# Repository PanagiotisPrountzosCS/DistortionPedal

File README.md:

# Custom distortion pedal implemented in kicad and ltspice

## This pedal is comprised of 3 stages:
  - Amplification
  - Clipping
  - Output Filtering

## The main branch contains a 100mm X 100mm PCB, while the 1590b-pcb branch contains a 35mm X 88mm PCB, which fits inside a 1590b box

## 1590b pcb

## 100mmx100mm pcb

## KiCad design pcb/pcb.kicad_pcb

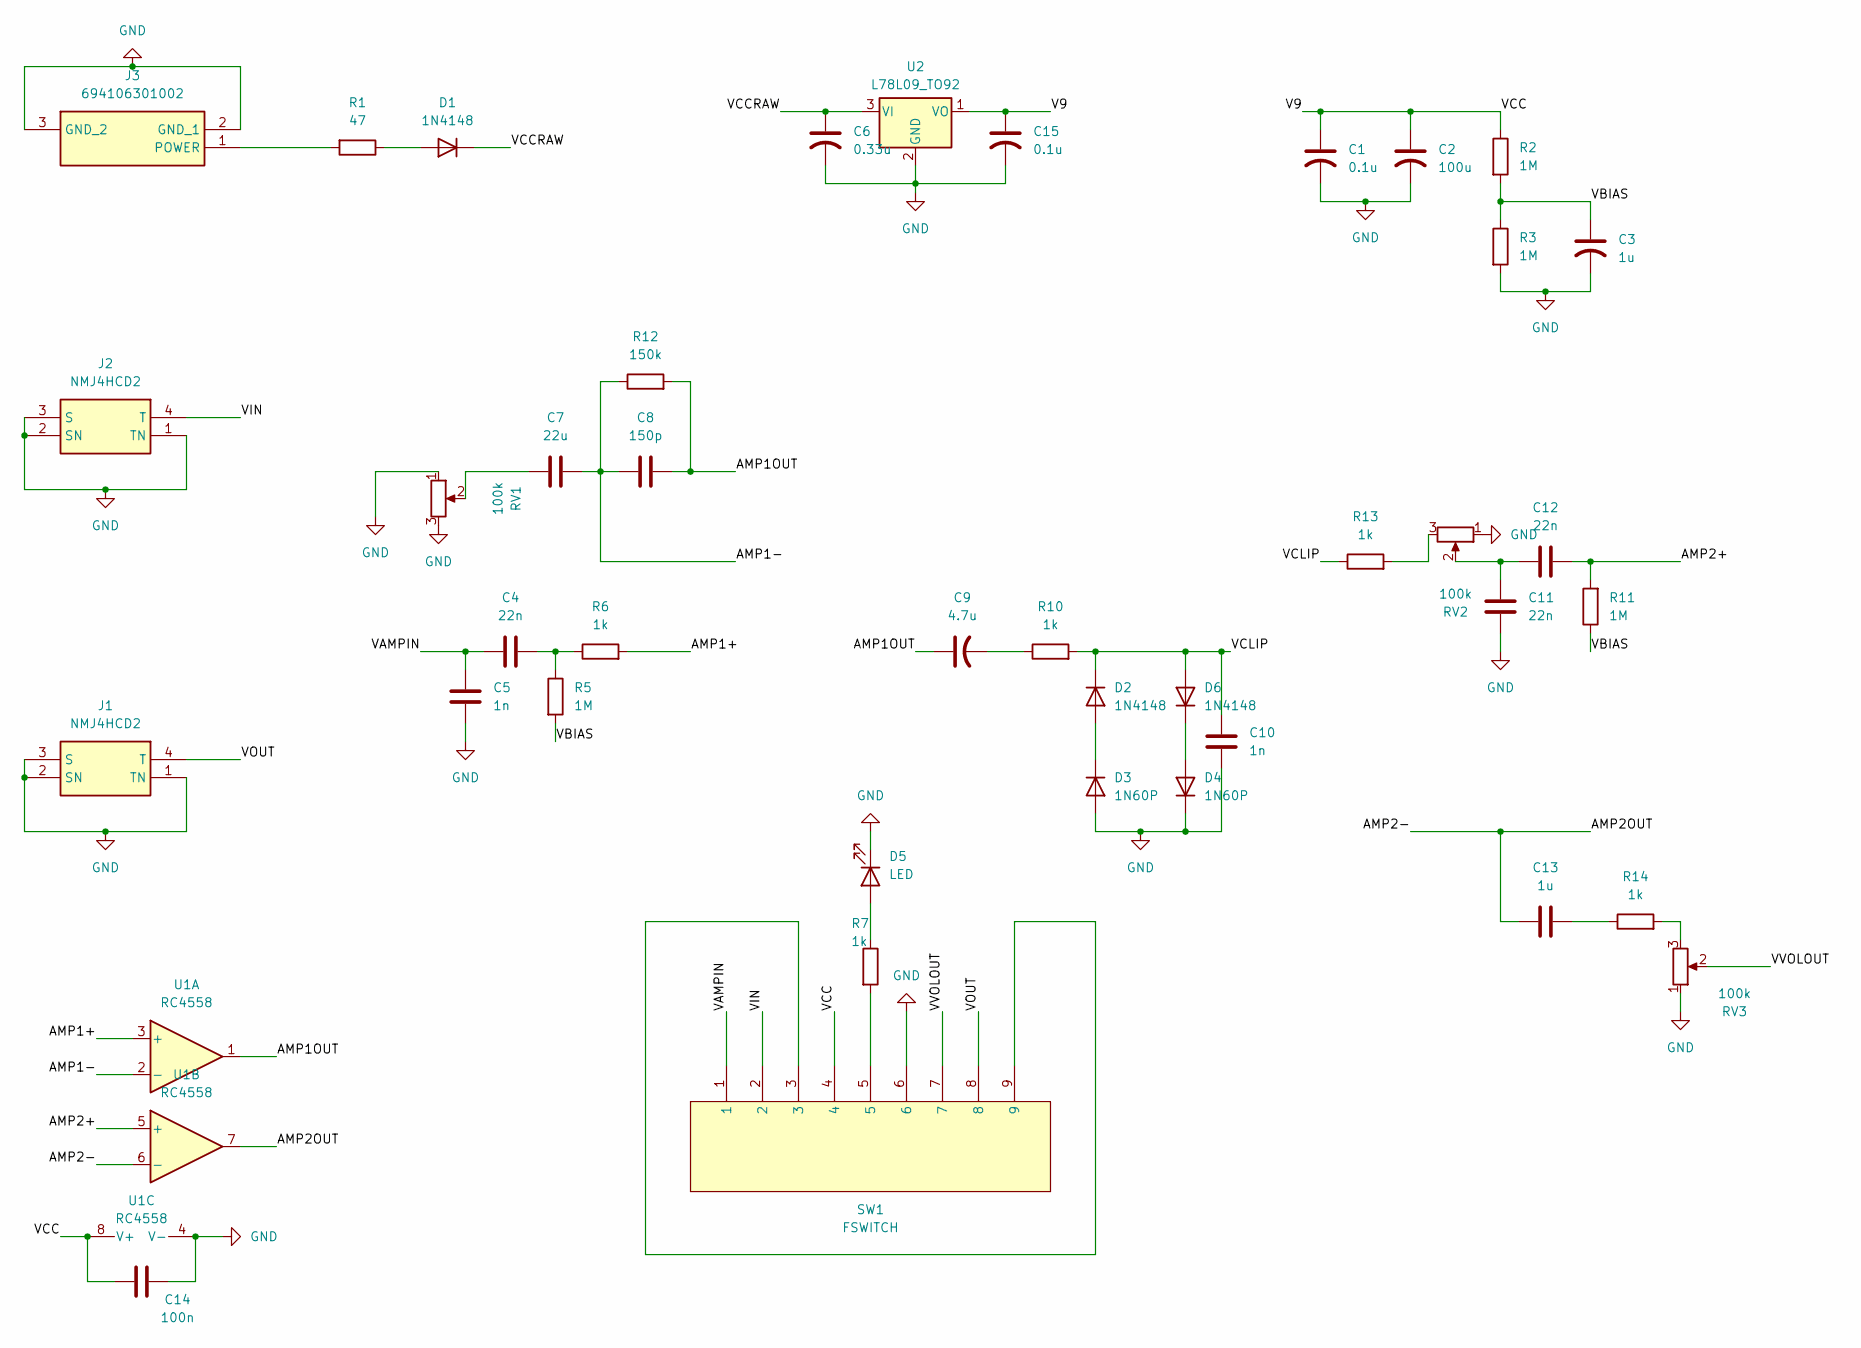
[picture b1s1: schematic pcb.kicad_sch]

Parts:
C1, C15: 0.1u; C_Radial_D5.0mm_H11.0mm_P2.00mm
C2: 100u; C_Radial_D6.3mm_H11.0mm_P2.50mm
C3: 1u; C_Radial_D6.3mm_H11.0mm_P2.50mm
C4, C12: 22n; C_Rect_L7.2mm_W2.5mm_P5.00mm
C5, C10: 1n; C_Disc_D3.0mm_W1.6mm_P2.50mm
C6: 0.33u; C_Radial_D5.0mm_H11.0mm_P2.00mm
C7: 22u; C_Radial_D5.0mm_H11.0mm_P2.00mm
C8: 150p; C_Disc_D3.0mm_W1.6mm_P2.50mm
C9: 4.7u; C_Radial_D5.0mm_H11.0mm_P2.00mm
C11: 22n; C_Disc_D3.0mm_W1.6mm_P2.50mm
C13: 1u; C_Rect_L7.2mm_W2.5mm_P5.00mm
C14: 100n; C_Disc_D3.0mm_W1.6mm_P2.50mm
D1, D2, D6: 1N4148; D_DO-35_SOD27_P7.62mm_Horizontal
D3, D4: 1N60P; D_DO-41_SOD81_P10.16mm_Horizontal
D5: LED; LED_D3.0mm
J1, J2: NMJ4HCD2; Mouser Part Number 550-12202
J3: 694106301002; Mouser Part Number 710-694106301002
R1: 47; R_Axial_DIN0207_L6.3mm_D2.5mm_P10.16mm_Horizontal
R2, R3, R5, R11: 1M; R_Axial_DIN0207_L6.3mm_D2.5mm_P10.16mm_Horizontal
R6, R7, R10, R13, R14: 1k; R_Axial_DIN0207_L6.3mm_D2.5mm_P10.16mm_Horizontal
R12: 150k; R_Axial_DIN0207_L6.3mm_D2.5mm_P10.16mm_Horizontal
RV1, RV2, RV3: 100k; Potentiometer_Omeg_PC16BU_Vertical
SW1: FSWITCH; 3PDT
U1: RC4558; CERDIP-8_W7.62mm_SideBrazed_LongPads_Socket
U2: L78L09_TO92; TO-92_Inline

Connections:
/AMP1+: R6.2, U1.3 (+)
/AMP1-: C7.2, C8.1, R12.1, U1.2 (-)
/AMP1OUT: C8.2, C9.1, R12.2, U1.1
/AMP2+: C12.2, R11.2, U1.5 (+)
/AMP2-: C13.1, U1.6 (-), U1.7
/V9: C1.1, C2.1, C14.2, C15.1, R2.1, SW1.4, U1.8 (V+), U2.1 (VO)
/VAMPIN: C4.1, C5.2, SW1.1
/VBIAS: C3.1, R2.2, R3.1, R5.2, R11.1
/VCCRAW: C6.1, D1.1 (K), U2.3 (VI)
/VCLIP: C10.2, D2.1 (K), D6.2 (A), R10.2, R13.1
/VIN: J2.4 (T), SW1.2
/VOUT: J1.4 (T), SW1.8
/VVOLOUT: RV3.2, SW1.7
GND: C1.2, C2.2, C3.2, C5.1, C6.2, C10.1, C11.2, C14.1, C15.2, D3.2 (A), D4.1 (K), D5.1 (K), J1.1 (TN), J1.2 (SN), J1.3 (S), J2.1 (TN), J2.2 (SN), J2.3 (S), J3.2 (GND_1), J3.3 (GND_2), R3.2, RV1.1, RV1.3, RV2.1, RV3.1, SW1.6, U1.4 (V-), U2.2 (GND)
unnamed: C4.2, R5.1, R6.1
unnamed: C7.1, RV1.2
unnamed: C9.2, R10.1
unnamed: C11.1, C12.1, RV2.2
unnamed: C13.2, R14.1
unnamed: D1.2 (A), R1.1
unnamed: D2.2 (A), D3.1 (K)
unnamed: D4.2 (A), D6.1 (K)
unnamed: D5.2 (A), R7.1
unnamed: J3.1 (POWER), R1.2
unnamed: R7.2, SW1.5
unnamed: R13.2, RV2.3
unnamed: R14.2, RV3.3
unnamed: SW1.3, SW1.9

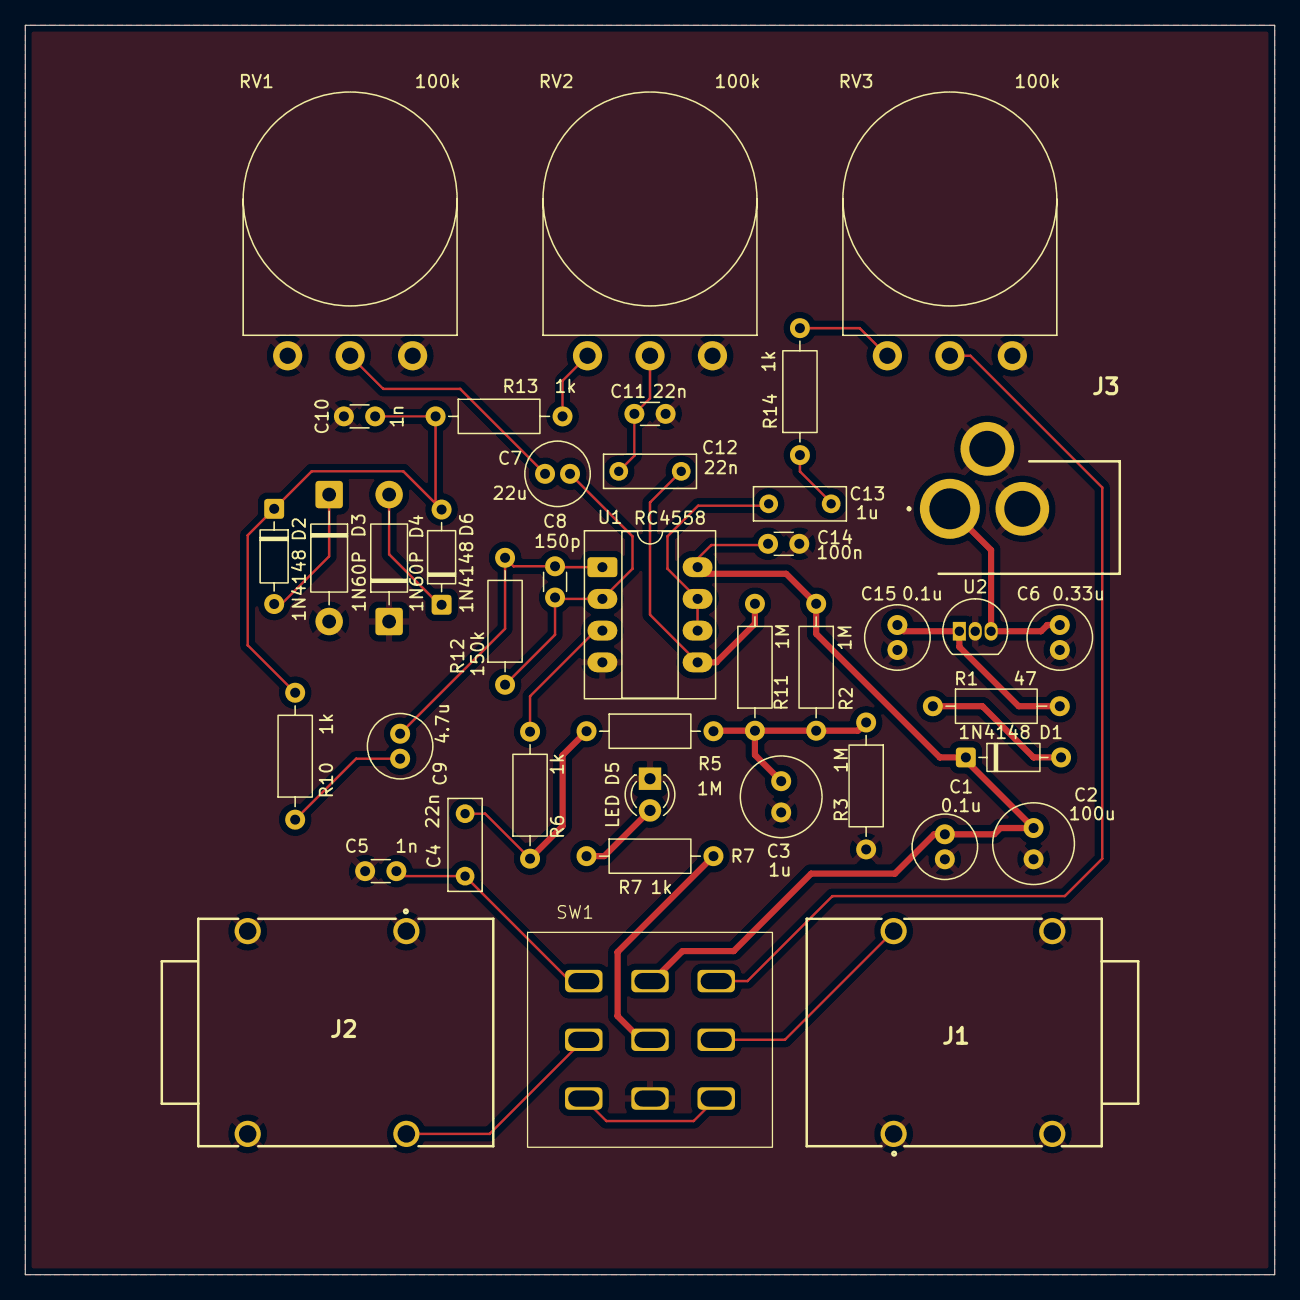
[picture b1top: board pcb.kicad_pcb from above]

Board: 2 copper layers, 100.0 x 100.0 mm, 41 parts (0 on the bottom side), 28 nets.

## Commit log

2026-04-06 First commit - Circuit implementation
2026-04-07 Finalize schematic
2026-04-08 Asymetric clipping
2026-04-19 FIRST PCB COMMIT! :D
2026-04-19 add 3pdt footprint and symbol
2026-04-19 FIX LIBRARIES :O
2026-04-19 Finalize pcb
2026-04-23 Rework Amplifier Stage
2026-04-26 Add README with project overview and PCB information
    Added project description and PCB details for distortion pedal.
2026-04-26 Add new image to README for PCB visualization
    Added an additional image to the README for better visualization.
2026-04-26 1590b pcb
2026-04-26 svg moai
2026-05-01 Fix reverse polarity protection diode - Move ahead of regulator
2026-05-01 Fix reverse polarity protection diode - schematic
